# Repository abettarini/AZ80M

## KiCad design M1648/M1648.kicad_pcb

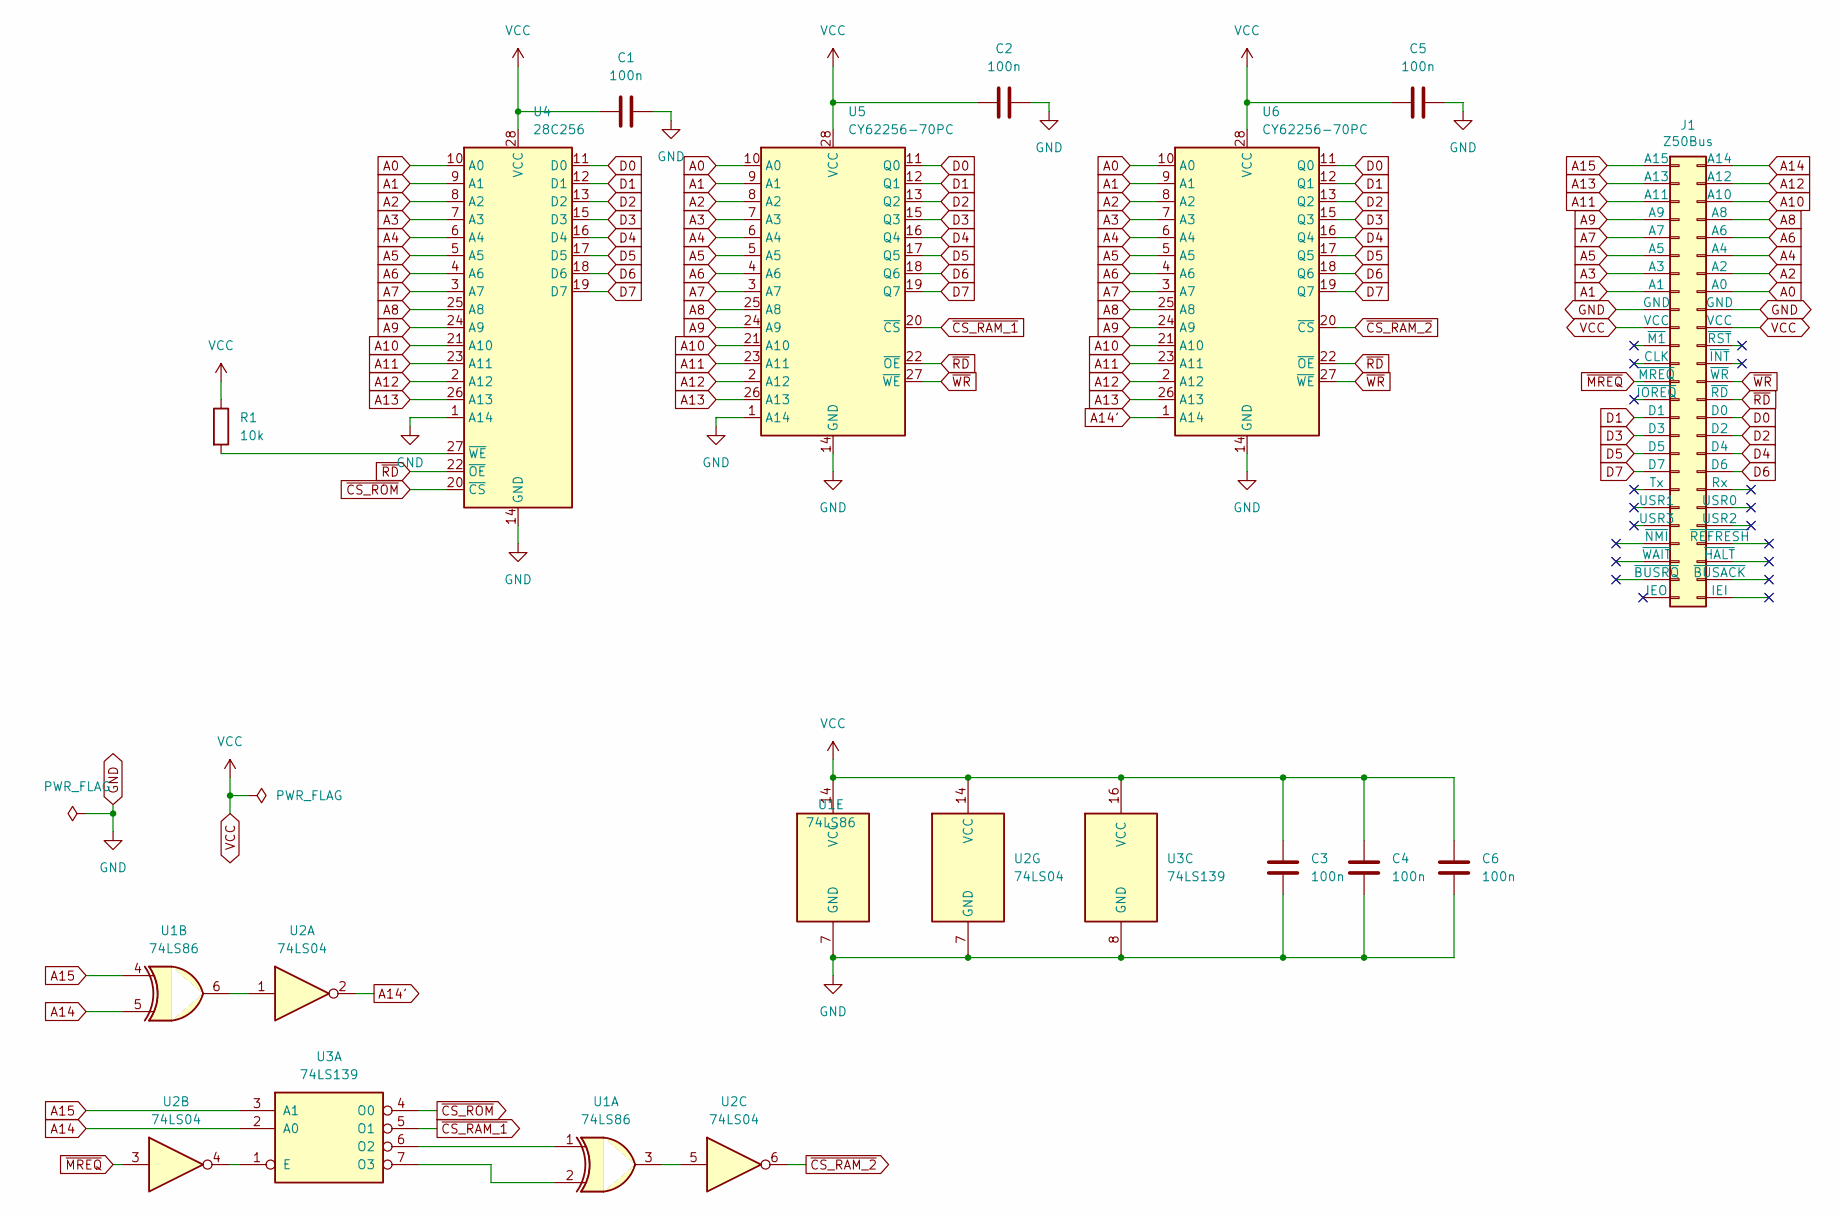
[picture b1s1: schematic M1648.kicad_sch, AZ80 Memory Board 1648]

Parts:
C1, C2, C3, C4, C5, C6: 100n; C_Disc_D3.8mm_W2.6mm_P2.50mm
J1: Z50Bus; PinHeader_2x25_P2.54mm_Horizontal
R1: 10k; R_Axial_DIN0204_L3.6mm_D1.6mm_P7.62mm_Horizontal
U1: 74LS86; DIP-14_W7.62mm
U2: 74LS04; DIP-14_W7.62mm
U3: 74LS139; DIP-16_W7.62mm
U4: 28C256; DIP-28_W15.24mm
U5, U6: CY62256-70PC; DIP-28_W15.24mm

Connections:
A0: J1.16 (A0), U4.10 (A0), U5.10 (A0), U6.10 (A0)
A1: J1.15 (A1), U4.9 (A1), U5.9 (A1), U6.9 (A1)
A2: J1.14 (A2), U4.8 (A2), U5.8 (A2), U6.8 (A2)
A3: J1.13 (A3), U4.7 (A3), U5.7 (A3), U6.7 (A3)
A4: J1.12 (A4), U4.6 (A4), U5.6 (A4), U6.6 (A4)
A5: J1.11 (A5), U4.5 (A5), U5.5 (A5), U6.5 (A5)
A6: J1.10 (A6), U4.4 (A6), U5.4 (A6), U6.4 (A6)
A7: J1.9 (A7), U4.3 (A7), U5.3 (A7), U6.3 (A7)
A8: J1.8 (A8), U4.25 (A8), U5.25 (A8), U6.25 (A8)
A9: J1.7 (A9), U4.24 (A9), U5.24 (A9), U6.24 (A9)
A10: J1.6 (A10), U4.21 (A10), U5.21 (A10), U6.21 (A10)
A11: J1.5 (A11), U4.23 (A11), U5.23 (A11), U6.23 (A11)
A12: J1.4 (A12), U4.2 (A12), U5.2 (A12), U6.2 (A12)
A13: J1.3 (A13), U4.26 (A13), U5.26 (A13), U6.26 (A13)
A14: J1.2 (A14), U1.5, U3.2 (A0)
A14': U2.2, U6.1 (A14)
A15: J1.1 (A15), U1.4, U3.3 (A1)
D0: J1.30 (D0), U4.11 (D0), U5.11 (Q0), U6.11 (Q0)
D1: J1.29 (D1), U4.12 (D1), U5.12 (Q1), U6.12 (Q1)
D2: J1.32 (D2), U4.13 (D2), U5.13 (Q2), U6.13 (Q2)
D3: J1.31 (D3), U4.15 (D3), U5.15 (Q3), U6.15 (Q3)
D4: J1.34 (D4), U4.16 (D4), U5.16 (Q4), U6.16 (Q4)
D5: J1.33 (D5), U4.17 (D5), U5.17 (Q5), U6.17 (Q5)
D6: J1.36 (D6), U4.18 (D6), U5.18 (Q6), U6.18 (Q6)
D7: J1.35 (D7), U4.19 (D7), U5.19 (Q7), U6.19 (Q7)
GND: C1.2, C2.2, C3.1, C4.1, C5.2, C6.2, J1.17 (GND), J1.18 (GND), U1.7 (GND), U2.7 (GND), U3.8 (GND), U4.1 (A14), U4.14 (GND), U5.1 (A14), U5.14 (GND), U6.14 (GND)
unnamed: R1.2, U4.27 (~WE)
unnamed: U1.1, U3.6 (O2)
unnamed: U1.2, U3.7 (O3)
unnamed: U1.3, U2.5
unnamed: U1.6, U2.1
unnamed: U2.4, U3.1 (E)
VCC: C1.1, C2.1, C3.2, C4.2, C5.1, C6.1, J1.19 (VCC), J1.20 (VCC), R1.1, U1.14 (VCC), U2.14 (VCC), U3.16 (VCC), U4.28 (VCC), U5.28 (VCC), U6.28 (VCC)
~CS_RAM_1: U3.5 (O1), U5.20 (~CS)
~CS_RAM_2: U2.6, U6.20 (~CS)
~CS_ROM: U3.4 (O0), U4.20 (~CS)
~MREQ: J1.25 (~MREQ), U2.3
~RD: J1.28 (~RD), U4.22 (~OE), U5.22 (~OE), U6.22 (~OE)
~WR: J1.26 (~WR), U5.27 (~WE), U6.27 (~WE)

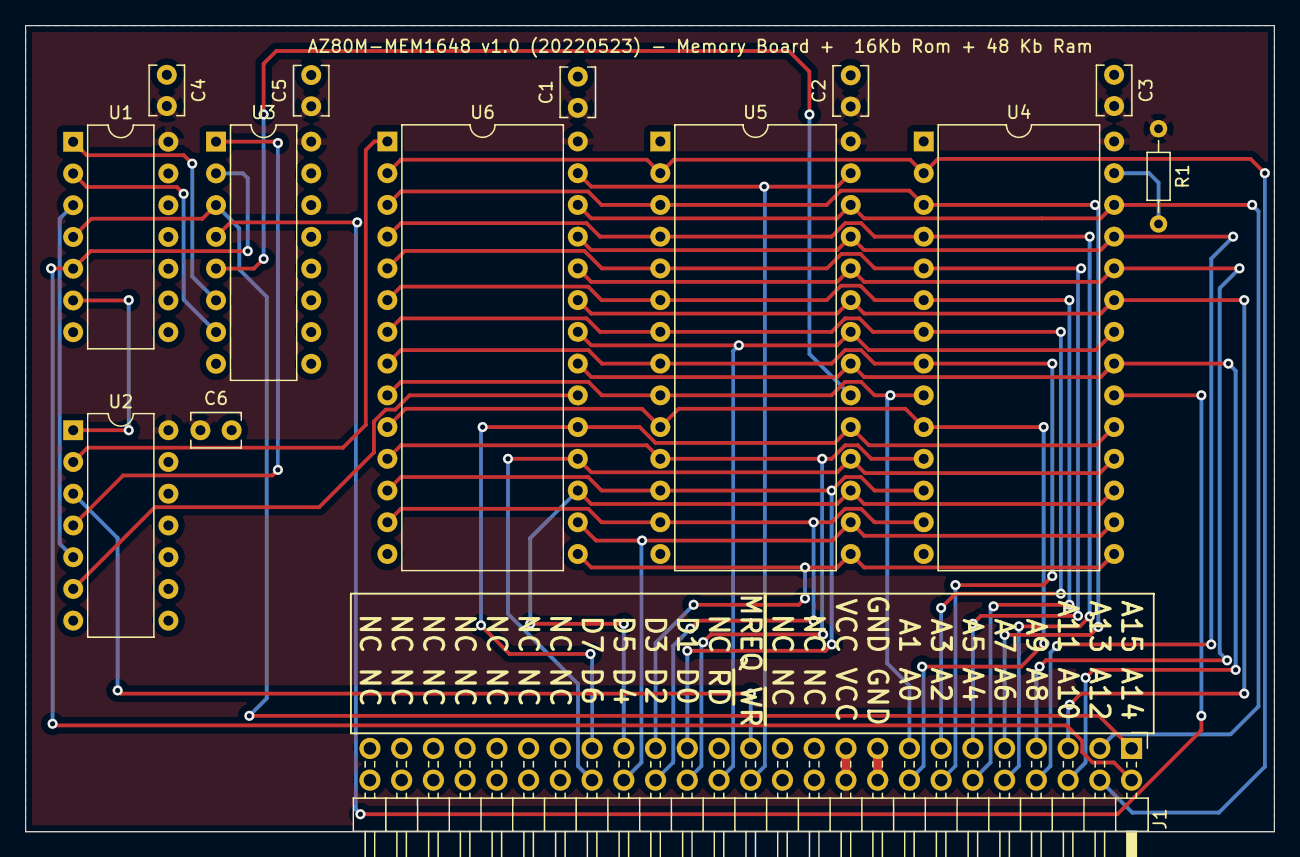
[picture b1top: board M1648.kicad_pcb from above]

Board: 2 copper layers, 99.9 x 64.5 mm, 14 parts (0 on the bottom side), 39 nets.

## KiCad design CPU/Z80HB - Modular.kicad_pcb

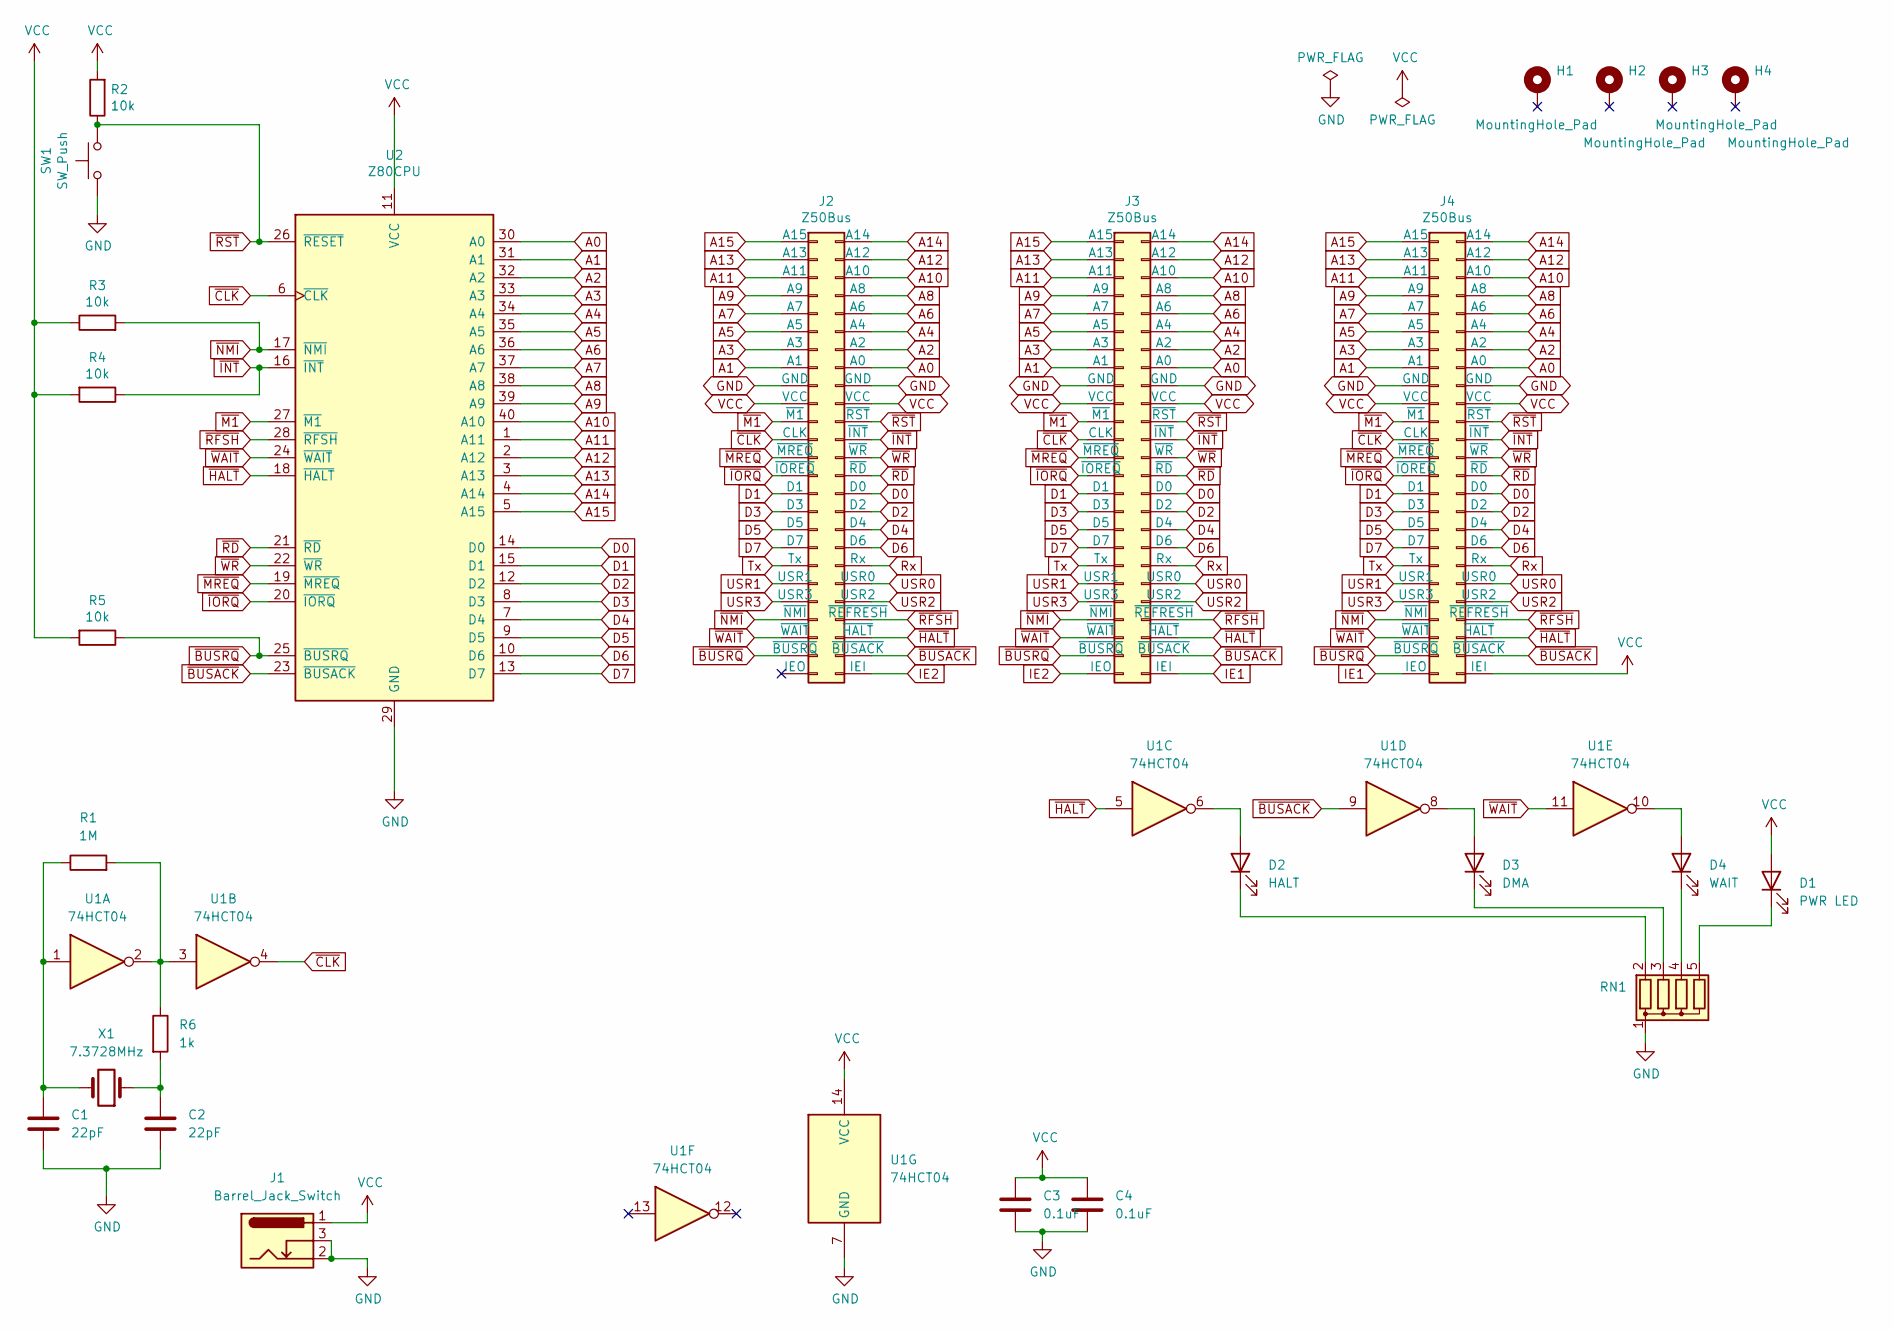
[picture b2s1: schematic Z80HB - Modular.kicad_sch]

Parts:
C1, C2: 22pF; C_Disc_D3.4mm_W2.1mm_P2.50mm
C3, C4: 0.1uF; C_Disc_D3.4mm_W2.1mm_P2.50mm
D1: PWR LED; LED_D5.0mm
D2: HALT; LED_D5.0mm
D3: DMA; LED_D5.0mm
D4: WAIT; LED_D5.0mm
H1, H2, H3, H4: MountingHole_Pad; MountingHole_2.2mm_M2_DIN965_Pad
J1: Barrel_Jack_Switch; BarrelJack_CUI_PJ-102AH_Horizontal
J2, J3, J4: Z50Bus; PinSocket_2x25_P2.54mm_Vertical
R1: 1M; R_Axial_DIN0207_L6.3mm_D2.5mm_P7.62mm_Horizontal
R2, R3, R4, R5: 10k; R_Axial_DIN0207_L6.3mm_D2.5mm_P7.62mm_Horizontal
R6: 1k; R_Axial_DIN0207_L6.3mm_D2.5mm_P7.62mm_Horizontal
RN1: (no value)
SW1: SW_Push; SW_PUSH_6mm_H5mm
U1: 74HCT04; DIP-14_W7.62mm
U2: Z80CPU; DIP-40_W15.24mm
X1: 7.3728MHz; Crystal_HC49-4H_Vertical

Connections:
A0: J2.16 (A0), J3.16 (A0), J4.16 (A0), U2.30 (A0)
A1: J2.15 (A1), J3.15 (A1), J4.15 (A1), U2.31 (A1)
A2: J2.14 (A2), J3.14 (A2), J4.14 (A2), U2.32 (A2)
A3: J2.13 (A3), J3.13 (A3), J4.13 (A3), U2.33 (A3)
A4: J2.12 (A4), J3.12 (A4), J4.12 (A4), U2.34 (A4)
A5: J2.11 (A5), J3.11 (A5), J4.11 (A5), U2.35 (A5)
A6: J2.10 (A6), J3.10 (A6), J4.10 (A6), U2.36 (A6)
A7: J2.9 (A7), J3.9 (A7), J4.9 (A7), U2.37 (A7)
A8: J2.8 (A8), J3.8 (A8), J4.8 (A8), U2.38 (A8)
A9: J2.7 (A9), J3.7 (A9), J4.7 (A9), U2.39 (A9)
A10: J2.6 (A10), J3.6 (A10), J4.6 (A10), U2.40 (A10)
A11: J2.5 (A11), J3.5 (A11), J4.5 (A11), U2.1 (A11)
A12: J2.4 (A12), J3.4 (A12), J4.4 (A12), U2.2 (A12)
A13: J2.3 (A13), J3.3 (A13), J4.3 (A13), U2.3 (A13)
A14: J2.2 (A14), J3.2 (A14), J4.2 (A14), U2.4 (A14)
A15: J2.1 (A15), J3.1 (A15), J4.1 (A15), U2.5 (A15)
D0: J2.30 (D0), J3.30 (D0), J4.30 (D0), U2.14 (D0)
D1: J2.29 (D1), J3.29 (D1), J4.29 (D1), U2.15 (D1)
D2: J2.32 (D2), J3.32 (D2), J4.32 (D2), U2.12 (D2)
D3: J2.31 (D3), J3.31 (D3), J4.31 (D3), U2.8 (D3)
D4: J2.34 (D4), J3.34 (D4), J4.34 (D4), U2.7 (D4)
D5: J2.33 (D5), J3.33 (D5), J4.33 (D5), U2.9 (D5)
D6: J2.36 (D6), J3.36 (D6), J4.36 (D6), U2.10 (D6)
D7: J2.35 (D7), J3.35 (D7), J4.35 (D7), U2.13 (D7)
GND: C1.2, C2.2, C3.2, C4.2, J1.2, J1.3, J2.17 (GND), J2.18 (GND), J3.17 (GND), J3.18 (GND), J4.17 (GND), J4.18 (GND), RN1.1 (common), SW1.1, U1.7 (GND), U2.29 (GND)
IE1: J3.50 (IEI), J4.49 (IEO)
IE2: J2.50 (IEI), J3.49 (IEO)
unnamed: C1.1, R1.1, U1.1, X1.2
unnamed: C2.1, R6.2, X1.1
unnamed: D1.1 (K), RN1.5 (R4)
unnamed: D2.1 (K), RN1.2 (R1)
unnamed: D2.2 (A), U1.6
unnamed: D3.1 (K), RN1.3 (R2)
unnamed: D3.2 (A), U1.8
unnamed: D4.1 (K), RN1.4 (R3)
unnamed: D4.2 (A), U1.10
unnamed: R1.2, R6.1, U1.2, U1.3
Rx: J2.38 (Rx), J3.38 (Rx), J4.38 (Rx)
Tx: J2.37 (Tx), J3.37 (Tx), J4.37 (Tx)
USR0: J2.40 (USR0), J3.40 (USR0), J4.40 (USR0)
USR1: J2.39 (USR1), J3.39 (USR1), J4.39 (USR1)
USR2: J2.42 (USR2), J3.42 (USR2), J4.42 (USR2)
USR3: J2.41 (USR3), J3.41 (USR3), J4.41 (USR3)
VCC: C3.1, C4.1, D1.2 (A), J1.1, J2.19 (VCC), J2.20 (VCC), J3.19 (VCC), J3.20 (VCC), J4.19 (VCC), J4.20 (VCC), J4.50 (IEI), R2.2, R3.1, R4.2, R5.2, U1.14 (VCC), U2.11 (VCC)
~BUSACK: J2.48 (~BUSACK), J3.48 (~BUSACK), J4.48 (~BUSACK), U1.9, U2.23 (~BUSACK)
~BUSRQ: J2.47 (~BUSRQ), J3.47 (~BUSRQ), J4.47 (~BUSRQ), R5.1, U2.25 (~BUSRQ)
~CLK: J2.23 (CLK), J3.23 (CLK), J4.23 (CLK), U1.4, U2.6 (~CLK)
~HALT: J2.46 (~HALT), J3.46 (~HALT), J4.46 (~HALT), U1.5, U2.18 (~HALT)
~INT: J2.24 (~INT), J3.24 (~INT), J4.24 (~INT), R4.1, U2.16 (~INT)
~IORQ: J2.27 (~IOREQ), J3.27 (~IOREQ), J4.27 (~IOREQ), U2.20 (~IORQ)
~M1: J2.21 (~M1), J3.21 (~M1), J4.21 (~M1), U2.27 (~M1)
~MREQ: J2.25 (~MREQ), J3.25 (~MREQ), J4.25 (~MREQ), U2.19 (~MREQ)
~NMI: J2.43 (~NMI), J3.43 (~NMI), J4.43 (~NMI), R3.2, U2.17 (~NMI)
~RD: J2.28 (~RD), J3.28 (~RD), J4.28 (~RD), U2.21 (~RD)
~RFSH: J2.44 (~REFRESH), J3.44 (~REFRESH), J4.44 (~REFRESH), U2.28 (~RFSH)
~RST: J2.22 (~RST), J3.22 (~RST), J4.22 (~RST), R2.1, SW1.2, U2.26 (~RESET)
~WAIT: J2.45 (~WAIT), J3.45 (~WAIT), J4.45 (~WAIT), U1.11, U2.24 (~WAIT)
~WR: J2.26 (~WR), J3.26 (~WR), J4.26 (~WR), U2.22 (~WR)

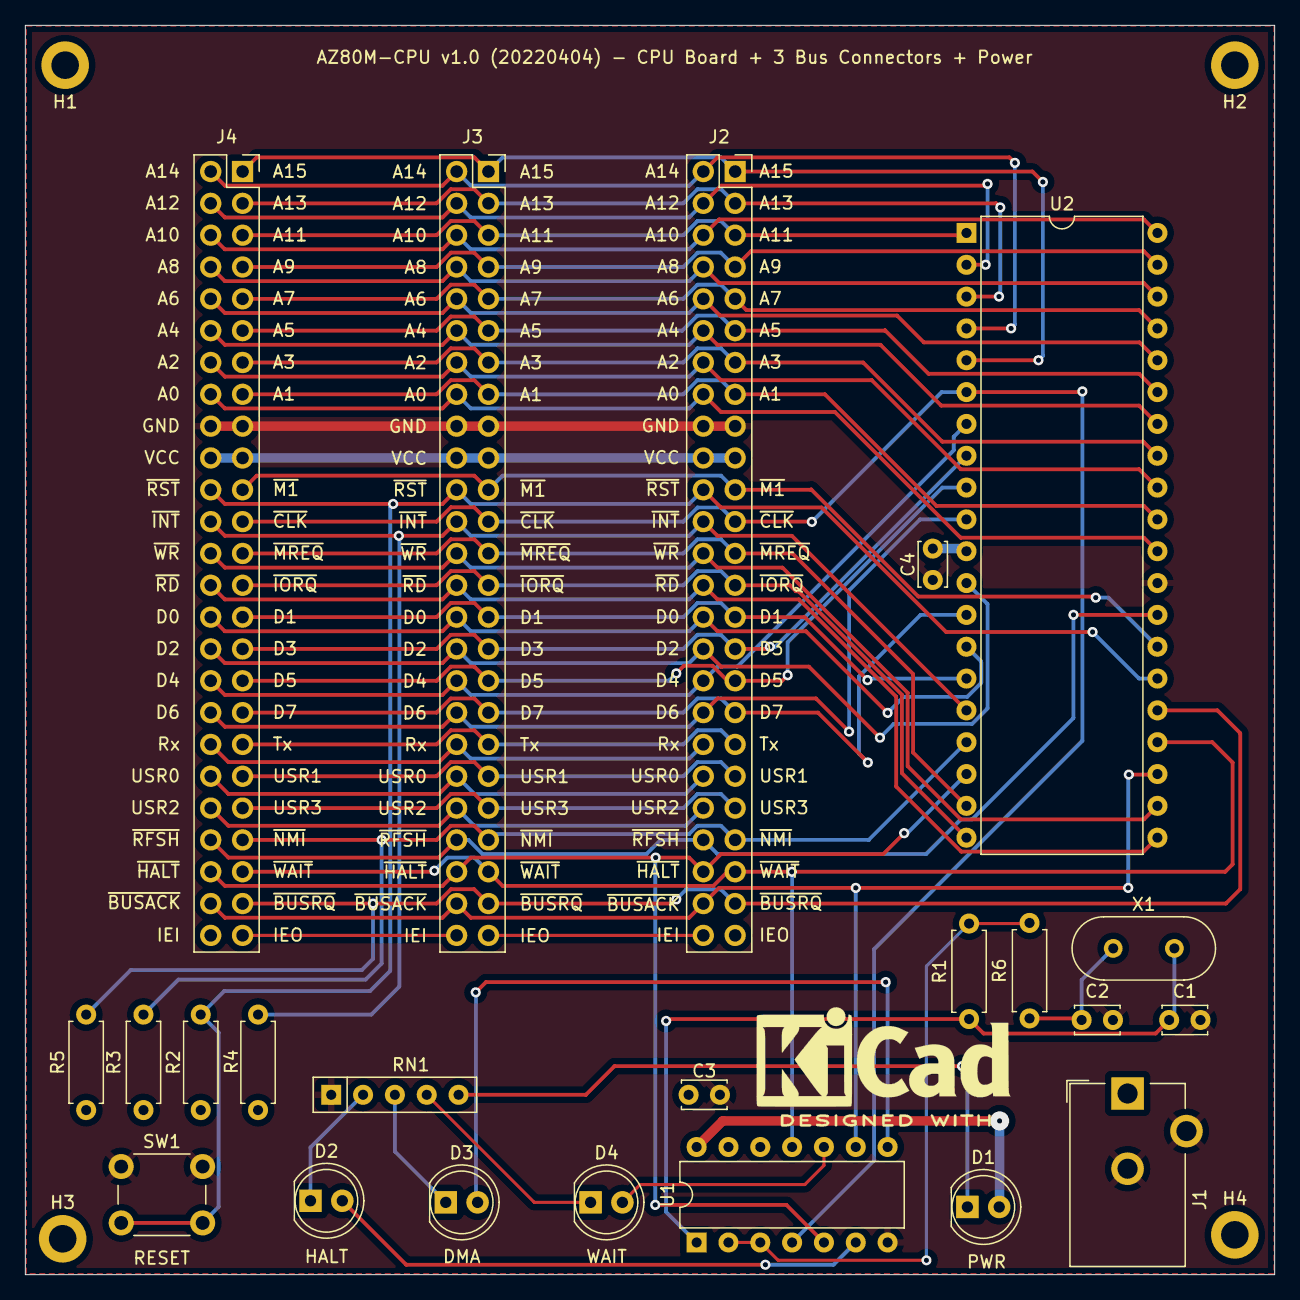
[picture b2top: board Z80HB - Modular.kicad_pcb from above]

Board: 2 copper layers, 99.7 x 99.7 mm, 27 parts (0 on the bottom side), 58 nets.

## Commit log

2022-05-23 Primo import
2022-05-23 Fix: il segnale A14' adesso è applicato a U6
2022-05-23 Aggiornata versione
2022-05-23 Modificato testo PCB
